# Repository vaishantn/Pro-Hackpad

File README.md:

# Pro-Hackpad
My version of a Macropad

## Preview
PCB Layout

## Schematic

## Top Plate

## Bottom Case

## Bill of Materials (BOM)

The following table lists the components required to assemble the project.

## Bill of Materials (BOM)

# Bill of Materials (BOM)

The following table lists the components required to assemble Starbie.

| Item | Qty | Description | Value | Manufacturer | Supplier |
|---:|---:|---|---|---|---|
| 1 | 2 | Addressable RGB LED, SK6812MINI, PLCC4 3535 package | SK6812MINI | OPSCO Optoelectronics | TME |
| 2 | 1 | 0.91-inch 128x32 SSD1306 I2C OLED module with 4-pin header | SSD1306 OLED 128x32 | Not identified by supplier | ShillehTek |
| 3 | 4 | CHERRY MX1A-C1NW 1u PCB-mount mechanical keyswitch, soft tactile, clear stem | CHERRY MX1A-C1NW | CHERRY | Mouser Electronics |
| 4 | 1 | Seeed Studio XIAO RP2040 microcontroller module (standard version) | XIAO-RP2040 | Seeed Studio | Seeed Studio |

# Made with:
-KiCad
-Autodesk Fusion
-Python

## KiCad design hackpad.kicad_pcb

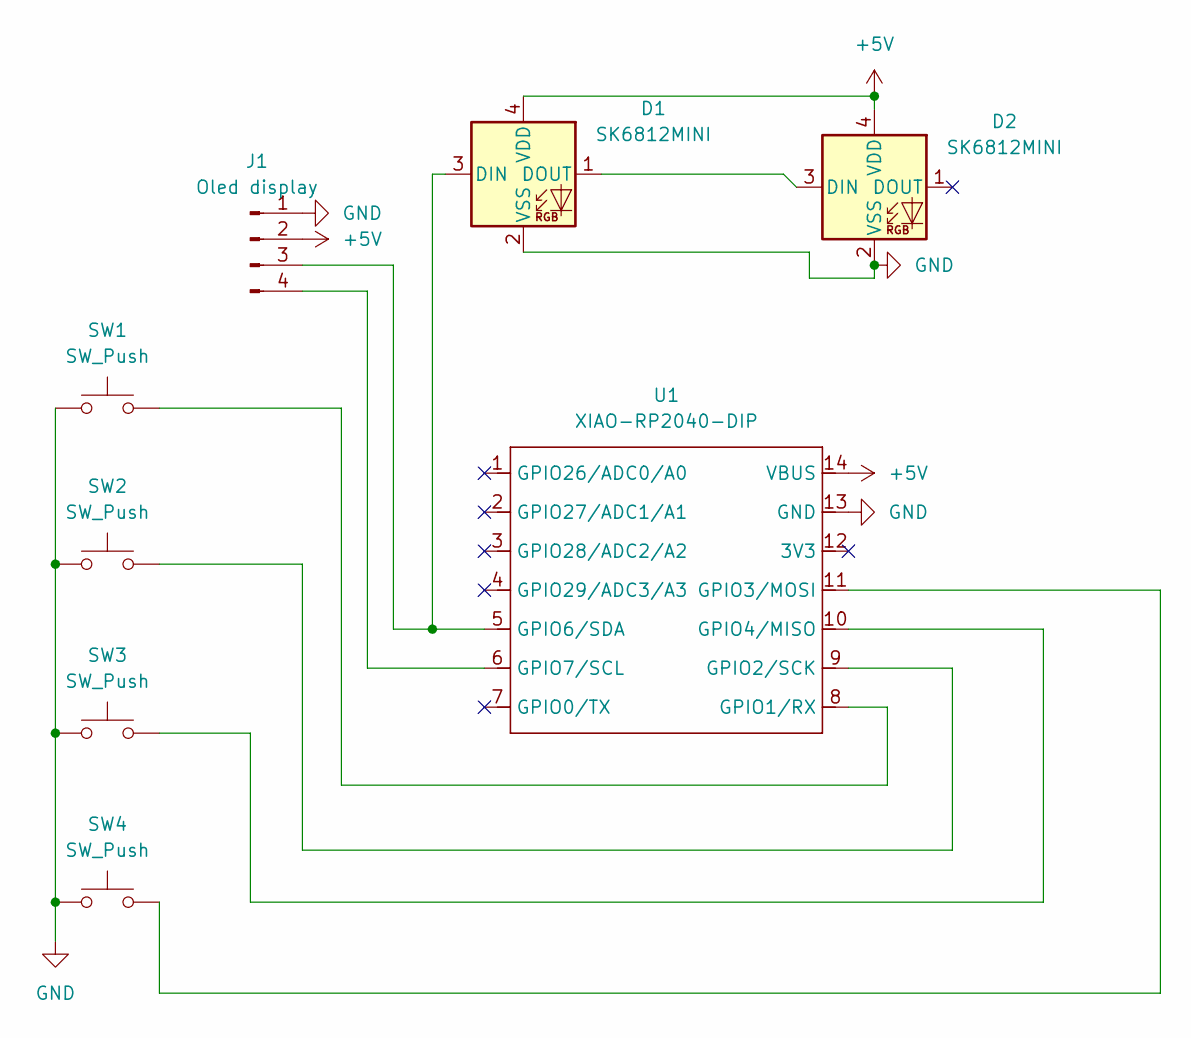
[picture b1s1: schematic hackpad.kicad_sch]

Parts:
D1, D2: SK6812MINI; LED_SK6812MINI_PLCC4_3.5x3.5mm_P1.75mm
J1: Oled display; SSD1306-0.91-OLED-4pin-128x32
SW1, SW2, SW3, SW4: SW_Push; SW_Cherry_MX_1.00u_PCB
U1: XIAO-RP2040-DIP

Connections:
+5V: D1.4 (VDD), D2.4 (VDD), J1.2, U1.14 (VBUS)
GND: D1.2 (VSS), D2.2 (VSS), J1.1, SW1.1, SW2.1, SW3.1, SW4.1, U1.13 (GND)
unnamed: D1.3 (DIN), J1.3, U1.5 (GPIO6/SDA)
unnamed: D1.1 (DOUT), D2.3 (DIN)
unnamed: J1.4, U1.6 (GPIO7/SCL)
unnamed: SW1.2, U1.8 (GPIO1/RX)
unnamed: SW2.2, U1.9 (GPIO2/SCK)
unnamed: SW4.2, U1.11 (GPIO3/MOSI)
unnamed: SW3.2, U1.10 (GPIO4/MISO)

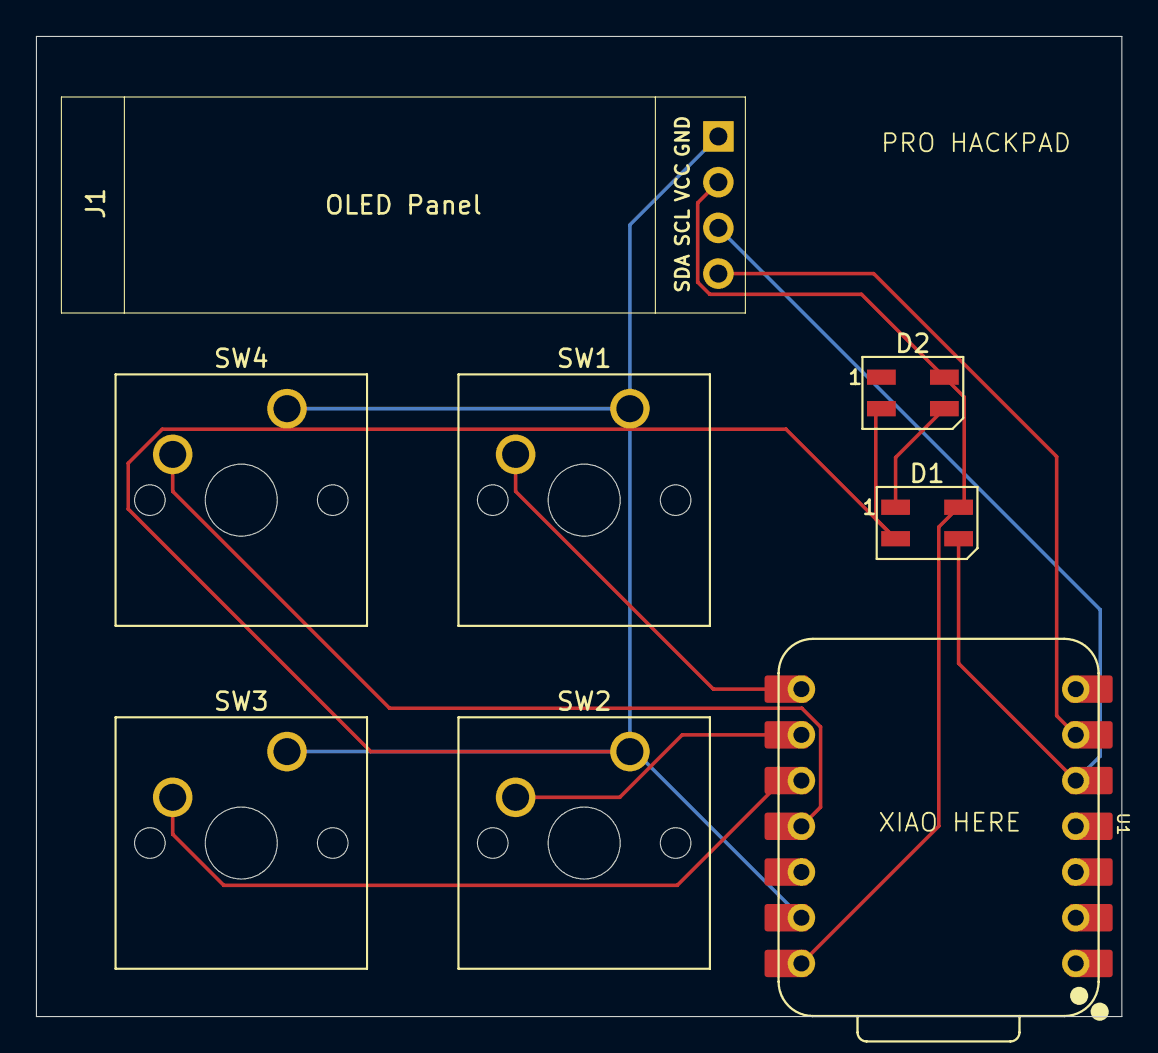
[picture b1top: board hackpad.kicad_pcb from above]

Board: 2 copper layers, 60.3 x 54.5 mm, 8 parts (0 on the bottom side), 9 nets.

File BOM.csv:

Item,References,Quantity,Description,Value,Footprint,Mounting Type,Assembly Method,DNP,Manufacturer,Manufacturer Part Number,Supplier,Supplier Part Number,Datasheet / Technical Documentation URL,Supplier Product URL,Notes
1,"D1, D2",2,"Addressable RGB LED, SK6812MINI, PLCC4 3535 package",SK6812MINI,LED_SMD:LED_SK6812MINI_PLCC4_3.5x3.5mm_P1.75mm,SMD (PLCC4),SMD reflow / PCBA,No,OPSCO Optoelectronics,SK6812MINI,TME,SK6812MINI,https://www.tme.com/Document/5fc48c8ad26fd0ea39de7670db3efc3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,https://www.tme.com/us/en-us/details/sk6812mini/smd-colour-l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,"D1 data output feeds D2 data input. TME identifies OPSCO MPN SK6812MINI; linked manufacturer document is for SK6812MINI-012, so confirm exact suffix/package and land pattern before PCBA. At VDD=5V, datasheet VIH minimum is 0.7 x VDD = 3.5V; XIAO RP2040 GPIO is 3.3V, so direct drive is not guaranteed—review a logic-level buffer or change the LED supply after electrical validation. KiCad footprint name is retained from the project."
2,J1,1,0.91-inch 128x32 SSD1306 I2C OLED module with 4-pin header,SSD1306 OLED 128x32,footprint:SSD1306-0.91-OLED-4pin-128x32,OLED module with 4-pin male header (THT interface),Manual module/header soldering; verify custom footprint against actual module,No,Not identified by supplier,,ShillehTek,AA321,https://cdn.shopify.com/s/files/1/0837/4340/8415/files/shill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,https://shillehtek.com/products/oled-ssd1306-128x32-i2c-0-91in,"Supplier SKU: AA321 (not a confirmed manufacturer part number). Supplier datasheet is marked PRELIMINARY; module supply range, current, dimensions and 5V tolerance are not documented. Schematic connects J1 pin 2 to +5V: obtain supplier confirmation before applying 5V. Supplier pin order is 1=GND, 2=VCC, 3=SCL, 4=SDA; verify J1 pad 3/4 nets and footprint orientation against the PCB before assembly. Datasheet does not identify an exact panel/module manufacturer or MPN."
3,"SW1, SW2, SW3, SW4",4,"CHERRY MX1A-C1NW 1u PCB-mount mechanical keyswitch, soft tactile, clear stem",CHERRY MX1A-C1NW,Button_Switch_Keyboard:SW_Cherry_MX_1.00u_PCB,Through-hole PC pins / PCB mount,"THT soldering (hand, wave or selective; confirm assembler capability)",No,CHERRY,MX1A-C1NW,Mouser Electronics,540-MX1A-C1NW,https://media.digikey.com/pdf/Data%20Sheets/Cherry%20PDFs/MX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,https://www.mouser.com/en/ProductDetail/CHERRY/MX1A-C1NW,"Specific orderable candidate matching the 1u Cherry MX PCB-mount style; Mouser describes this model as soft tactile, clear stem, 65cN. Confirm that this feel/force is intended before purchasing all four. Check the exact KiCad footprint pad layout against the manufacturer drawing."
4,U1,1,Seeed Studio XIAO RP2040 microcontroller module (standard version),XIAO-RP2040,Seeed_Studio_XIAO_Series Library:XIAO-RP2040-DIP,Pre-built XIAO module; castellated / carrier-board footprint,Module soldering to carrier PCB; confirm exact footprint and assembly-house support,No,Seeed Studio,102010428,Seeed Studio,102010428,https://wiki.seeedstudio.com/XIAO-RP2040/,https://www.seeedstudio.com/XIAO-RP2040-v1-0-p-5026.html,"Standard XIAO RP2040, Seeed SKU/order code: 102010428. Seeed specifies 3.3V general-purpose I/O and warns that input voltages above 3.3V may damage the MCU. Confirm this custom module footprint against the exact module revision. The linked Raspberry Pi datasheet covers the RP2040 MCU; the Seeed wiki is the board-level documentation. Raspberry Pi RP2040 MCU datasheet: https://datasheets.raspberrypi.com/rp2040/rp2040-datasheet.pdf."
